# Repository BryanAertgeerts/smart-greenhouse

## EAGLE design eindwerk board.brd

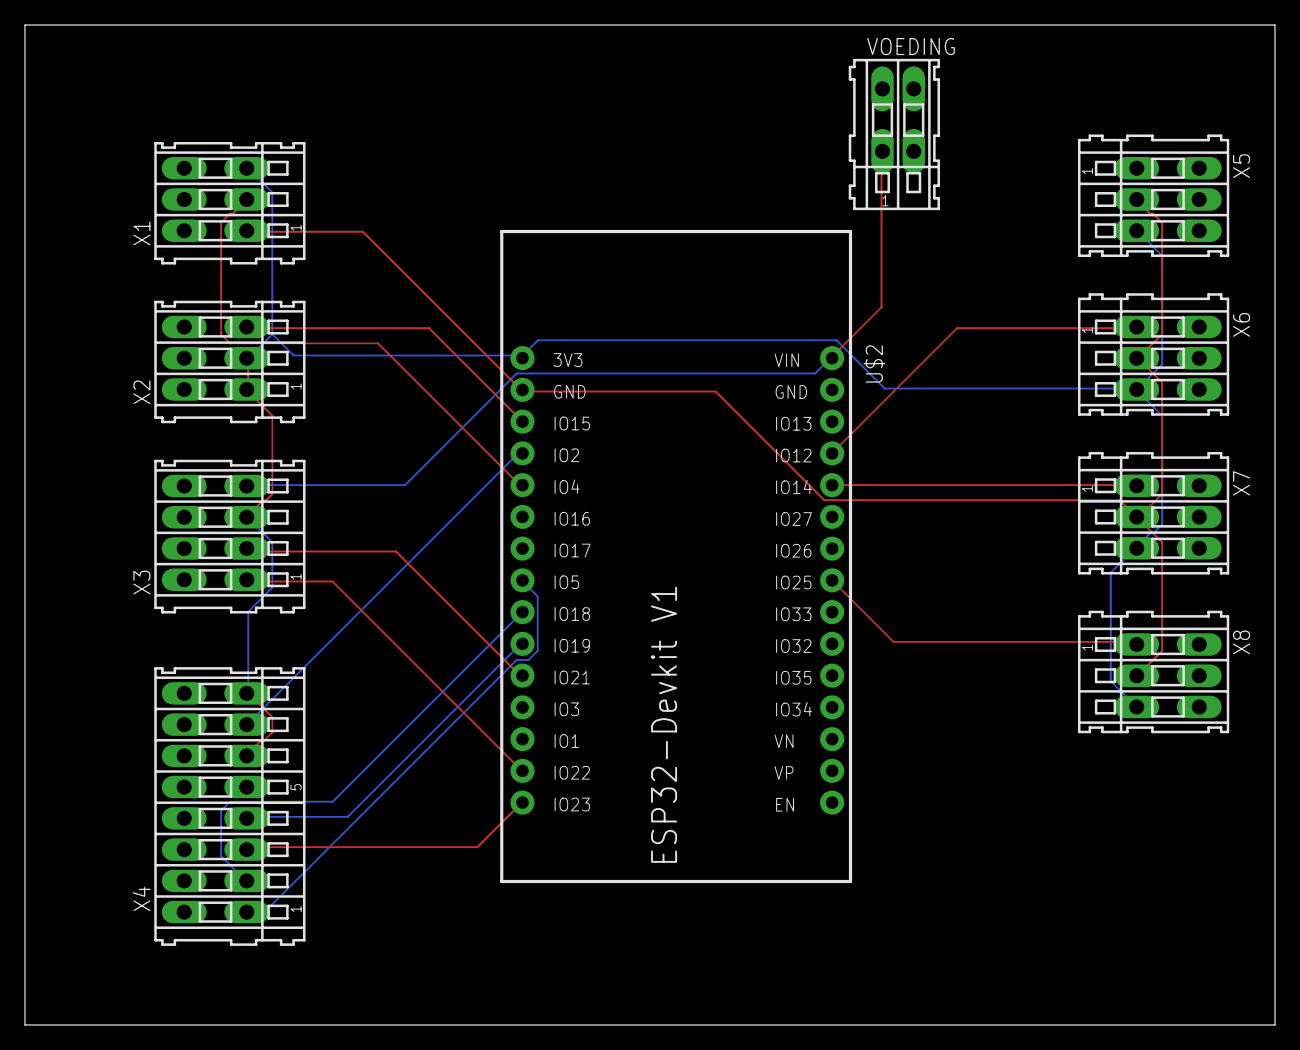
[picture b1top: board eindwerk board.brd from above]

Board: 2 copper layers, 100.0 x 80.0 mm, 10 parts (0 on the bottom side), 17 nets.

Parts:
U$2: ESP32DEVKITV1; ESP32-DEVKITV1
VOEDING: 233-102
X1, X2, X5, X6, X7, X8: 233-103
X3: 233-104
X4: 233-108

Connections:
unnamed: U$2.28, X5.B1
unnamed: U$2.2, X1.B1, X5.B2, X6.B2, X7.B2, X8.B2
unnamed: U$2.27, X6.B1
unnamed: U$2.30, VOEDING.B1, X3.B4
unnamed: U$2.26, X7.B1
unnamed: U$2.5, X1.B2
unnamed: U$2.4, X4.B7
unnamed: U$2.23, X8.B1
unnamed: U$2.11, X3.B2
unnamed: U$2.14, X3.B1
unnamed: U$2.10, X4.B4
unnamed: U$2.15, X4.B3
unnamed: U$2.9, X4.B2
unnamed: U$2.8, X4.B1
unnamed: U$2.3, X2.B3
unnamed: U$2.1, X1.B3, X2.B1, X2.B2, X3.B3, X4.B6, X4.B8, X5.B3, X6.B3, X7.B3, X8.B3
unnamed: U$2.28, VOEDING.B2
